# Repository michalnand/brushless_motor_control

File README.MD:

# stm32 FOC brushless motor controller

# repository

## utils : [utils](utils)
- testing utils and simulations
- transformation tests : transform_test.py
- PI current synthetis : pi_torque.ipynb
- LQR synthetis : lqr_design.ipynb
- requires [LibsControll](https://github.com/michalnand/libs_control)

## hardware : [hardware](hardware)
- eagle files
- 3D priting parts (jig for magnet centering)
- IMPORTANT - in schematic is wrong MP6540HA, correct is MP6540H (pwm only driver with enable)

- MCU   : stm32f051, arm cortex m0, 48MHz
- 3phase driver : MP6540H (DONT MP6540HA), 5A, 50V
- encoder : AS5600, 12bit, i2c

## firmware : [firmware](firmware)
- main code for stm32f051
- core is in **user** folder
- see motor.cpp and motor_control.cpp to understand all details

# FOC block diagrams

# transformation tests

basic tranformations tests :
- clarke - park - pwm scaling
- see [transform_test.py](utils/transform_test.py)

# fast running transformations in fixed point

## key features

- sine and cosine is precomputed, 1024 values arrays
- angle 2pi == 1024 (or 0) into tables
- theta ranges from <0, 1023>
- SINE_TABLE_MAX  represents "one", 1023 in tables
- square root of 3 is also precomputed, as fraction of x/1024 
- all divisions are by power of 2 - to avoid slow division
- this can easily run few kHz on cortex m0 (48MHz ARM)

```c++

#define SQRT3       ((int32_t)1773)      // sqrt(3)     = 1773/1024
#define SQRT3INV    ((int32_t)591)       // 1/sqrt(3)   = 591/1024

void Motor::set_park(int32_t d, int32_t q, uint32_t theta)
{
    //inverse Park transform
    int32_t alpha = (d*cos_tab(theta) - q*sin_tab(theta))/SINE_TABLE_MAX;
    int32_t beta  = (d*sin_tab(theta) + q*cos_tab(theta))/SINE_TABLE_MAX;

    this->set_clarke(alpha, beta);
}

void Motor::set_clarke(int32_t alpha, int32_t beta)
{
    //inverse Clarke transform
    int32_t a = alpha;
    int32_t b = -(alpha/2) + (SQRT3*beta)/(2*1024);
    int32_t c = -(alpha/2) - (SQRT3*beta)/(2*1024);

    this->set_phases(a, b, c); 
}

void Motor::set_phases(int32_t a, int32_t b, int32_t c)
{
    //transform into space-vector modulation, to achieve full voltage range
    int32_t min_val = min3(a, b, c);
    int32_t max_val = max3(a, b, c); 

    int32_t com_val = (min_val + max_val)/2;  

    //normalise into 0..MOTOR_CONTROL_MAX
    int32_t a_pwm = ((a - com_val)*SQRT3INV)/1024 + MOTOR_CONTROL_MAX/2;
    int32_t b_pwm = ((b - com_val)*SQRT3INV)/1024 + MOTOR_CONTROL_MAX/2;
    int32_t c_pwm = ((c - com_val)*SQRT3INV)/1024 + MOTOR_CONTROL_MAX/2;

    a_pwm = clamp((a_pwm*PWM_PERIOD)/MOTOR_CONTROL_MAX, 0, PWM_PERIOD);
    b_pwm = clamp((b_pwm*PWM_PERIOD)/MOTOR_CONTROL_MAX, 0, PWM_PERIOD);
    c_pwm = clamp((c_pwm*PWM_PERIOD)/MOTOR_CONTROL_MAX, 0, PWM_PERIOD);

    set_pwm(a_pwm, b_pwm, c_pwm);
}
```

# fast running PID in fixed point

- controller is first discretised in constructor 
- dt is sampling period in miliseconds
- kp, ki, kd are common controller constants, multiplied by 16384, to avoid floating point

```c++
k0 = kp + ((ki*dt)/1000) + ((kd*1000)/dt);
k1 = -kp - 2*((kd*1000)/dt);
k2 = ((kd*1000)/dt); 
```

- whole PID is just 3 multiplications and 4 additions
- to avoid integral windup, only clamping output is necessary 

```c++
int32_t PID::step(int32_t error)
{
    this->e2 = this->e1;
    this->e1 = this->e0;
    this->e0 = error;

    int32_t du = (k0*e0 + k1*e1 + k2*e2)/16384;
    u+= du;

    //anti windup
    if (u > antiwindup_max)
    {
        u = antiwindup_max;
    }
    
    if (u < antiwindup_min)
    {
        u = antiwindup_min;
    }

    return u;
}
```

# LQR position controller

see [lqr_design.ipynb](utils/lqr_design.ipynb)

## whole controller structure

## closed loop response + disturbance rejection

## poles

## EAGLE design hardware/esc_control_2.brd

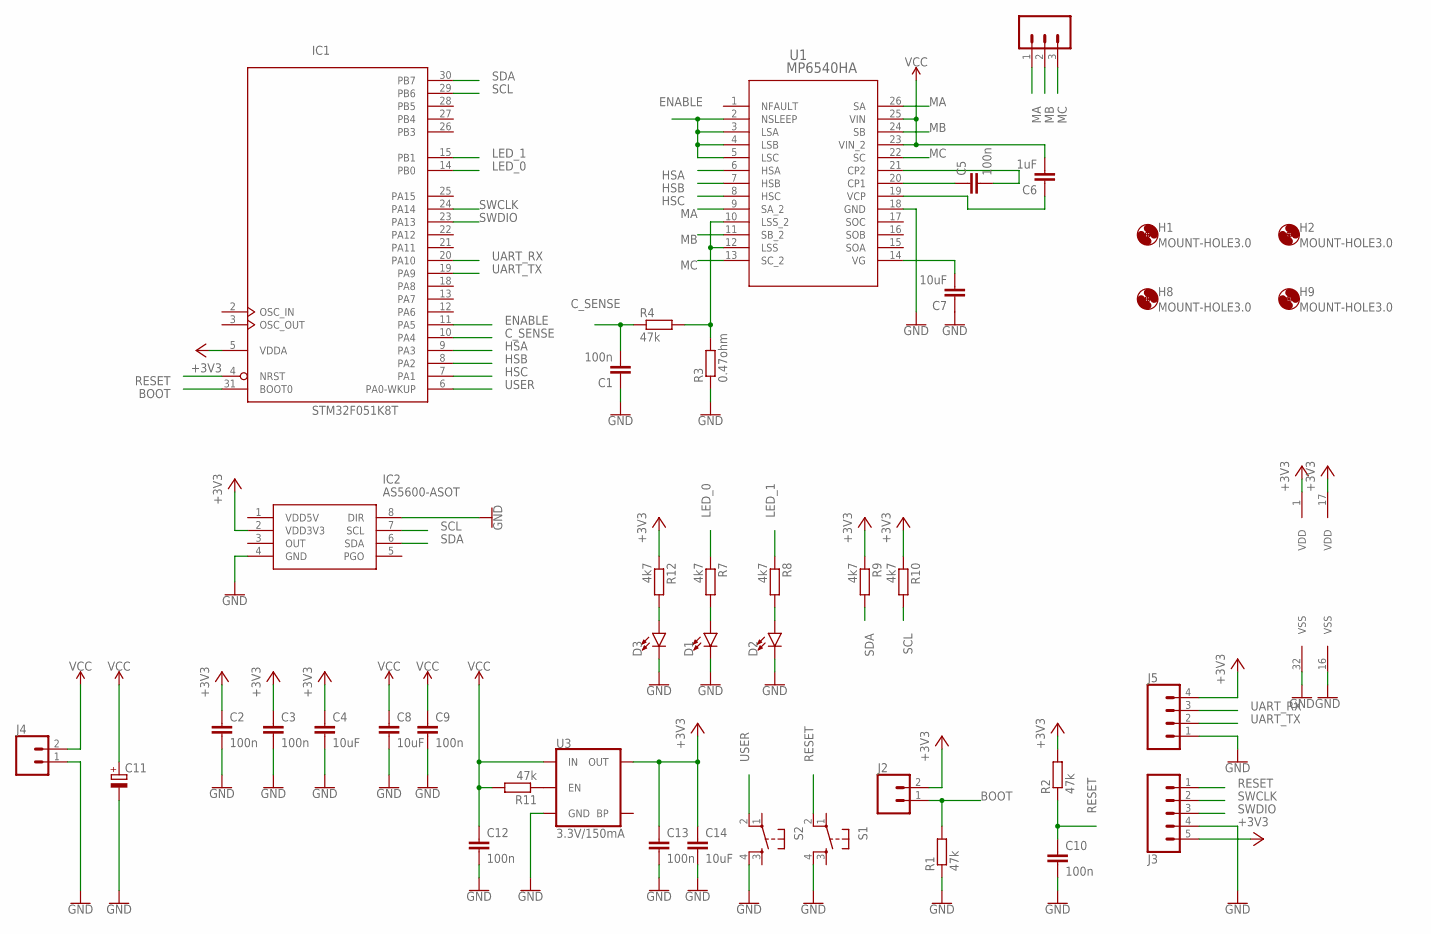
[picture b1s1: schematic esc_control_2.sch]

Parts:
C1, C2, C3, C5, C9, C10, C12, C13: 100n; C0805
C4, C7, C8, C14: 10uF; C0805
C6: 1uF; C0805
C11: CPOL-EU153CLV-0605; 153CLV-0605
D1, D2, D3: LED1206; LED-1206
H1, H2, H8, H9: MOUNT-HOLE3.0; 3,0
IC1: STM32F051K8T; LQFP32
IC2: AS5600-ASOT; SOIC127P600X175-8N
J1: 455-1750-1-ND; 1X03
J2, J4: CONN_02PTH3; 1X02_LONGPADS
J3: CONN_05PTH_LONGPADS; 1X05_LONGPADS
J5: CONN_04LONGPADS; 1X04_LONGPADS
R1, R2, R4, R11: 47k; M0805
R3: 0.47ohm; R2512
R7, R8, R9, R10, R12: 4k7; M0805
S1, S2: TAC_SWITCHSMD; TACTILE-SWITCH-SMD
U1: MP6540HA; QFN-5X5_MP6540HA_MNP
U3: 3.3V/150mA; SOT23-5

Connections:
+3V3: C2.1, C3.1, C4.1, C13.1, C14.1, IC1.1 (VDD), IC1.5 (VDDA), IC1.17 (VDD), IC2.2 (VDD3V3), J2.2, J3.5, J5.4, R2.2, R9.1, R10.1, R12.1, U3.5 (OUT)
BOOT: IC1.31 (BOOT0), J2.1, R1.2
C_SENSE: C1.2, IC1.10 (PA4), R4.1
ENABLE: IC1.11 (PA5), U1.2 (NSLEEP), U1.3 (LSA), U1.4 (LSB), U1.5 (LSC)
GND: C1.1, C2.2, C3.2, C4.2, C7.1, C8.2, C9.2, C10.2, C11.-, C12.2, C13.2, C14.2, D1.C, D2.C, D3.C, IC1.16 (VSS), IC1.32 (VSS), IC2.4 (GND), IC2.8 (DIR), J3.4, J4.1, J5.1, R1.1, R3.1, S1.4, S2.4, U1.18 (GND), U3.2 (GND)
HSA: IC1.9 (PA3), U1.6 (HSA)
HSB: IC1.8 (PA2), U1.7 (HSB)
HSC: IC1.7 (PA1), U1.8 (HSC)
LED_0: IC1.14 (PB0), R7.1
LED_1: IC1.15 (PB1), R8.1
MA: J1.1, U1.9 (SA_2), U1.26 (SA)
MB: J1.2, U1.11 (SB_2), U1.24 (SB)
MC: J1.3, U1.13 (SC_2), U1.22 (SC)
unnamed: C5.1, U1.20 (CP1)
unnamed: C5.2, U1.21 (CP2)
unnamed: C6.1, U1.19 (VCP)
unnamed: C7.2, U1.14 (VG)
unnamed: D1.A, R7.2
unnamed: D2.A, R8.2
unnamed: R11.1, U3.3 (EN)
unnamed: D3.A, R12.2
unnamed: R3.2, R4.2, U1.10 (LSS_2), U1.12 (LSS)
RESET: C10.1, IC1.4 (NRST), J3.1, R2.1, S1.2
SCL: IC1.29 (PB6), IC2.7 (SCL), R10.2
SDA: IC1.30 (PB7), IC2.6 (SDA), R9.2
SWCLK: IC1.24 (PA14), J3.2
SWDIO: IC1.23 (PA13), J3.3
UART_RX: IC1.20 (PA10), J5.3
UART_TX: IC1.19 (PA9), J5.2
USER: IC1.6 (PA0-WKUP), S2.2
VCC: C6.2, C8.1, C9.1, C11.+, C12.1, J4.2, R11.2, U1.23 (VIN_2), U1.25 (VIN), U3.1 (IN)

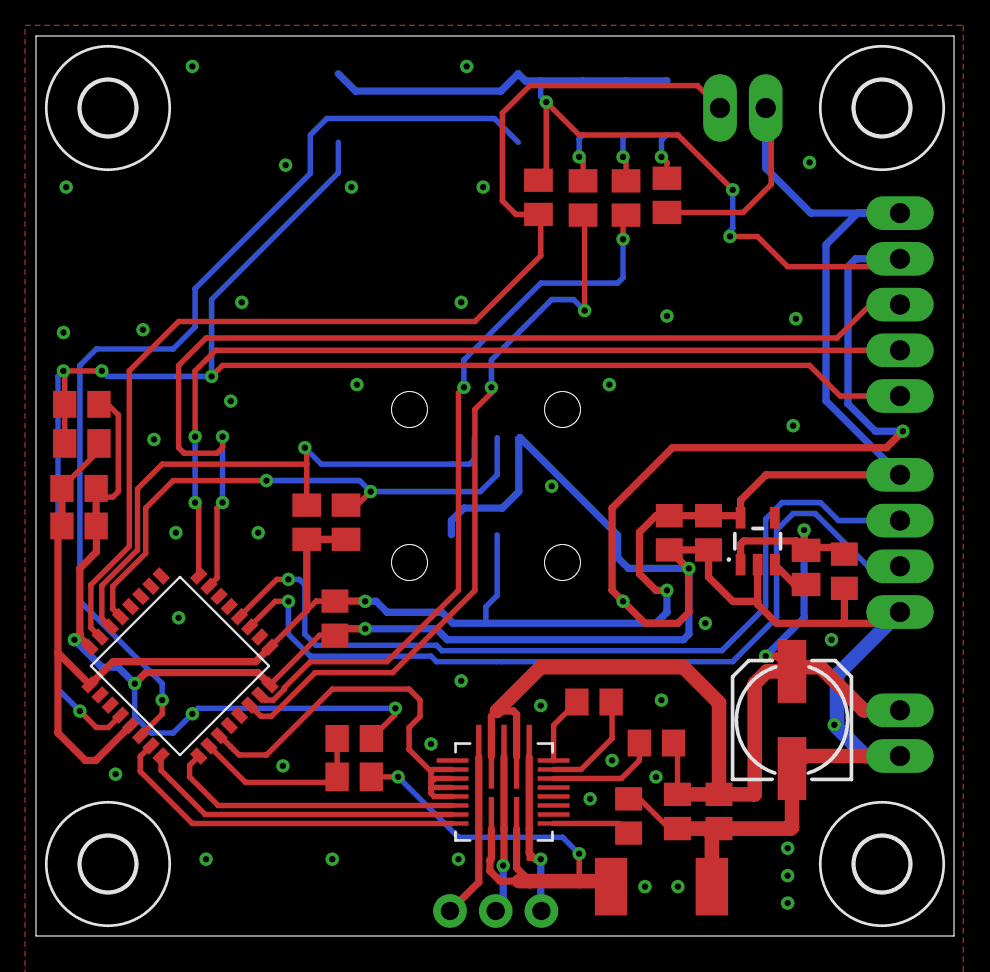
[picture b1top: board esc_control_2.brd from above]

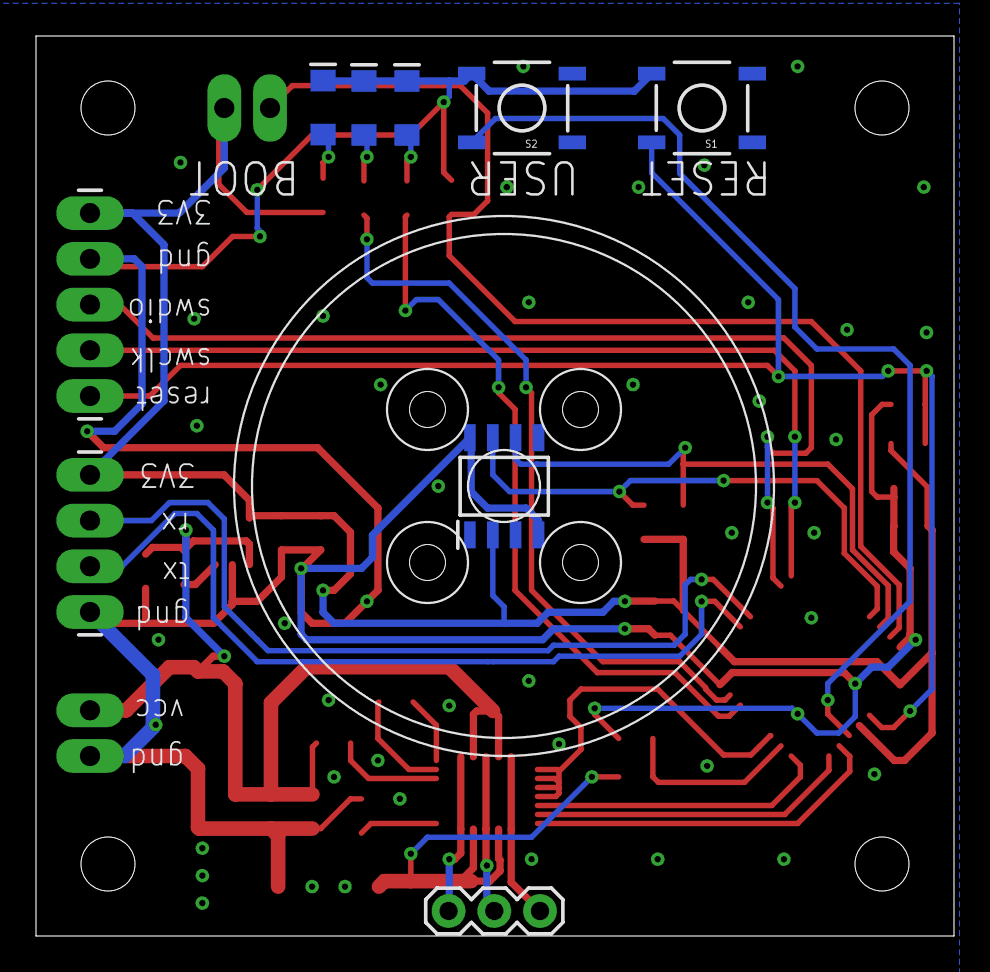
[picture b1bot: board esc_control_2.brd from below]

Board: 2 copper layers, 51.0 x 50.0 mm, 43 parts (12 on the bottom side), 31 nets.

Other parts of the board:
U$1: BRUSHLESS_GIMBAL_MOTOR_2204

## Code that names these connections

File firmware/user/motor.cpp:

#include "motor.h"

#include <gonio.h>
#include <device.h>


//helping stuff
#define SQRT3       ((int32_t)1773)      // sqrt(3)     = 1773/1024
#define SQRT3INV    ((int32_t)591)       // 1/sqrt(3)   = 591/1024

#define max2(x,y) (((x) >= (y)) ? (x) : (y))
#define min2(x,y) (((x) <= (y)) ? (x) : (y))

#define max3(x, y, z) (max2(max2(x, y), z))
#define min3(x, y, z) (min2(min2(x, y), z))


Motor::Motor()
{
    
}

Motor::~Motor()
{

}

void Motor::init()
{
    this->hw_init();
}


void Motor::hold()
{
    this->set_torque(500, 0, 0);

    uint32_t loops = 4000000;
    while (loops--) 
    {
        __asm("nop"); 
    } 
}
    

void Motor::release()
{
    this->set_torque(0, 0, 0);

    uint32_t loops = 4000000;
    while (loops--) 
    {
        __asm("nop"); 
    } 
}
    


void Motor::set_torque(int32_t torque, uint32_t phase, uint32_t rotor_angle)
{
    int32_t q = (torque*cos_tab(phase))/SINE_TABLE_MAX;
    int32_t d = (torque*sin_tab(phase))/SINE_TABLE_MAX;

    this->set_park(d, q, (rotor_angle*MOTOR_POLES)/(2*4));
}

 
void Motor::set_park(int32_t d, int32_t q, uint32_t theta)
{
    //inverse Park transform
    int32_t alpha = (d*cos_tab(theta) - q*sin_tab(theta))/SINE_TABLE_MAX;
    int32_t beta  = (d*sin_tab(theta) + q*cos_tab(theta))/SINE_TABLE_MAX;

    this->set_clarke(alpha, beta);
}

void Motor::set_clarke(int32_t alpha, int32_t beta)
{
    //inverse Clarke transform
    int32_t a = alpha;
    int32_t b = -(alpha/2) + (SQRT3*beta)/(2*1024);
    int32_t c = -(alpha/2) - (SQRT3*beta)/(2*1024);


    this->set_phases(a, b, c); 
}

void Motor::set_phases(int32_t a, int32_t b, int32_t c)
{
    //transform into space-vector modulation, to achieve full voltage range
    int32_t min_val = min3(a, b, c);
    int32_t max_val = max3(a, b, c); 

    int32_t com_val = (min_val + max_val)/2;  

    //normalise into 0..MOTOR_CONTROL_MAX
    int32_t a_pwm = ((a - com_val)*SQRT3INV)/1024 + MOTOR_CONTROL_MAX/2;
    int32_t b_pwm = ((b - com_val)*SQRT3INV)/1024 + MOTOR_CONTROL_MAX/2;
    int32_t c_pwm = ((c - com_val)*SQRT3INV)/1024 + MOTOR_CONTROL_MAX/2;
    
     
    a_pwm = clamp((a_pwm*PWM_PERIOD)/MOTOR_CONTROL_MAX, 0, PWM_PERIOD);
    b_pwm = clamp((b_pwm*PWM_PERIOD)/MOTOR_CONTROL_MAX, 0, PWM_PERIOD);
    c_pwm = clamp((c_pwm*PWM_PERIOD)/MOTOR_CONTROL_MAX, 0, PWM_PERIOD);

    set_pwm(a_pwm, b_pwm, c_pwm);
}



void Motor::hw_init()
{
    GPIO_InitTypeDef GPIO_InitStruct;
    
    //PWM controll pins 
    //PWMA : PA3, TIM2_CH4
    //PWMB : PA2, TIM2_CH3
    //PWMC : PA1, TIM2_CH2

    //RCC_APB1PeriphClockCmd(RCC_AHBPeriph_GPIOA, ENABLE);

    RCC->AHBENR|= RCC_AHBENR_GPIOAEN;
 
    
    //init pins
    GPIO_InitStruct.GPIO_Pin    = GPIO_Pin_1 | GPIO_Pin_2 | GPIO_Pin_3;
    GPIO_InitStruct.GPIO_OType  = GPIO_OType_PP;
    GPIO_InitStruct.GPIO_PuPd   = GPIO_PuPd_NOPULL;
    GPIO_InitStruct.GPIO_Mode   = GPIO_Mode_AF;
    GPIO_InitStruct.GPIO_Speed  = GPIO_Speed_10MHz;
    GPIO_Init(GPIOA, &GPIO_InitStruct);

    //alternating functions for pins
    GPIO_PinAFConfig(GPIOA, GPIO_PinSource3, GPIO_AF_2);
    GPIO_PinAFConfig(GPIOA, GPIO_PinSource2, GPIO_AF_2);
    GPIO_PinAFConfig(GPIOA, GPIO_PinSource1, GPIO_AF_2);
    


    //enable controll pin, PA5
    RCC->AHBENR|= RCC_AHBENR_GPIOAEN;
    
    //init pins
    GPIO_InitStruct.GPIO_Pin    = GPIO_Pin_5;
    GPIO_InitStruct.GPIO_OType  = GPIO_OType_PP;
    GPIO_InitStruct.GPIO_PuPd   = GPIO_PuPd_NOPULL;
    GPIO_InitStruct.GPIO_Mode   = GPIO_Mode_OUT;
    GPIO_InitStruct.GPIO_Speed  = GPIO_Speed_Level_1;
    GPIO_Init(GPIOA, &GPIO_InitStruct);

    


    //init timer 2

    TIM_TimeBaseInitTypeDef TIM_BaseStruct;

    //enable clock for timer 2
    RCC_APB1PeriphClockCmd(RCC_APB1Periph_TIM2, ENABLE);
    //RCC->AHBENR|= RCC_APB1ENR_TIM2EN;

    
    // PWM_frequency = timer_clk / (TIM_Period + 1)
    // TIM_Period = timer_clk / PWM_frequency - 1
    TIM_BaseStruct.TIM_Prescaler    = 0;
    TIM_BaseStruct.TIM_CounterMode  = TIM_CounterMode_Up;

    TIM_BaseStruct.TIM_Period               = PWM_PERIOD;
    TIM_BaseStruct.TIM_ClockDivision        = TIM_CKD_DIV1;
    TIM_BaseStruct.TIM_RepetitionCounter    = 0;
	 
    // Initialize TIM2
    TIM_TimeBaseInit(TIM2, &TIM_BaseStruct);
    TIM_Cmd(TIM2, ENABLE);

    //stop motor    
    this->set_pwm(0, 0, 0);

    //set enable to high, for all phases
    GPIOA->ODR |= (1<<5); 
}


void Motor::set_pwm(uint32_t a_pwm, uint32_t b_pwm, uint32_t c_pwm)
{
    //PWM output settings
    TIM_OCInitTypeDef TIM_OCStruct;
    
    // PWM mode 2 : clear on compare match
    // PWM mode 1 : set on compare match
    TIM_OCStruct.TIM_OCMode         = TIM_OCMode_PWM2;
    TIM_OCStruct.TIM_OutputState    = TIM_OutputState_Enable;
    TIM_OCStruct.TIM_OCPolarity     = TIM_OCPolarity_Low;

    //HSA pwm, PA3, TIM2_CH4
    TIM_OCStruct.TIM_Pulse = b_pwm;
    TIM_OC4Init(TIM2, &TIM_OCStruct);
    TIM_OC4PreloadConfig(TIM2, TIM_OCPreload_Enable);

    //HSB pwm, PA2, TIM2_CH3
    TIM_OCStruct.TIM_Pulse = a_pwm;
    TIM_OC3Init(TIM2, &TIM_OCStruct);
    TIM_OC3PreloadConfig(TIM2, TIM_OCPreload_Enable);

    //HSC pwm, PA1, TIM2_CH2
    TIM_OCStruct.TIM_Pulse = c_pwm;
    TIM_OC2Init(TIM2, &TIM_OCStruct);
    TIM_OC2PreloadConfig(TIM2, TIM_OCPreload_Enable);
}



int32_t Motor::clamp(int32_t value, int32_t min, int32_t max)
{
    if (value > max)
    {
        value = max;
    }

    if (value < min)
    {
        value = min;
    }

    return value;
}

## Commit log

2023-03-15 hardware done
2023-03-15 initial firmware
2023-03-15 motor control basic
2023-03-16 first tests
2023-03-19 pi controller
2023-04-09 first working code
2023-04-12 working controller
2023-04-15 documentation
2023-04-29 lqr updated
2023-05-21 filter for position
2023-06-04 new firmware
2023-07-09 fixed antiwindup

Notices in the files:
parts and their libraries:
SparkFun-Connectors: Licensing: Creative Commons ShareAlike 4.0 International - https://creativecommons.org/licenses/by-sa/4.0
COPYRIGHT: Copyright (C) 2018 Accelerated Designs. All rights reserved
